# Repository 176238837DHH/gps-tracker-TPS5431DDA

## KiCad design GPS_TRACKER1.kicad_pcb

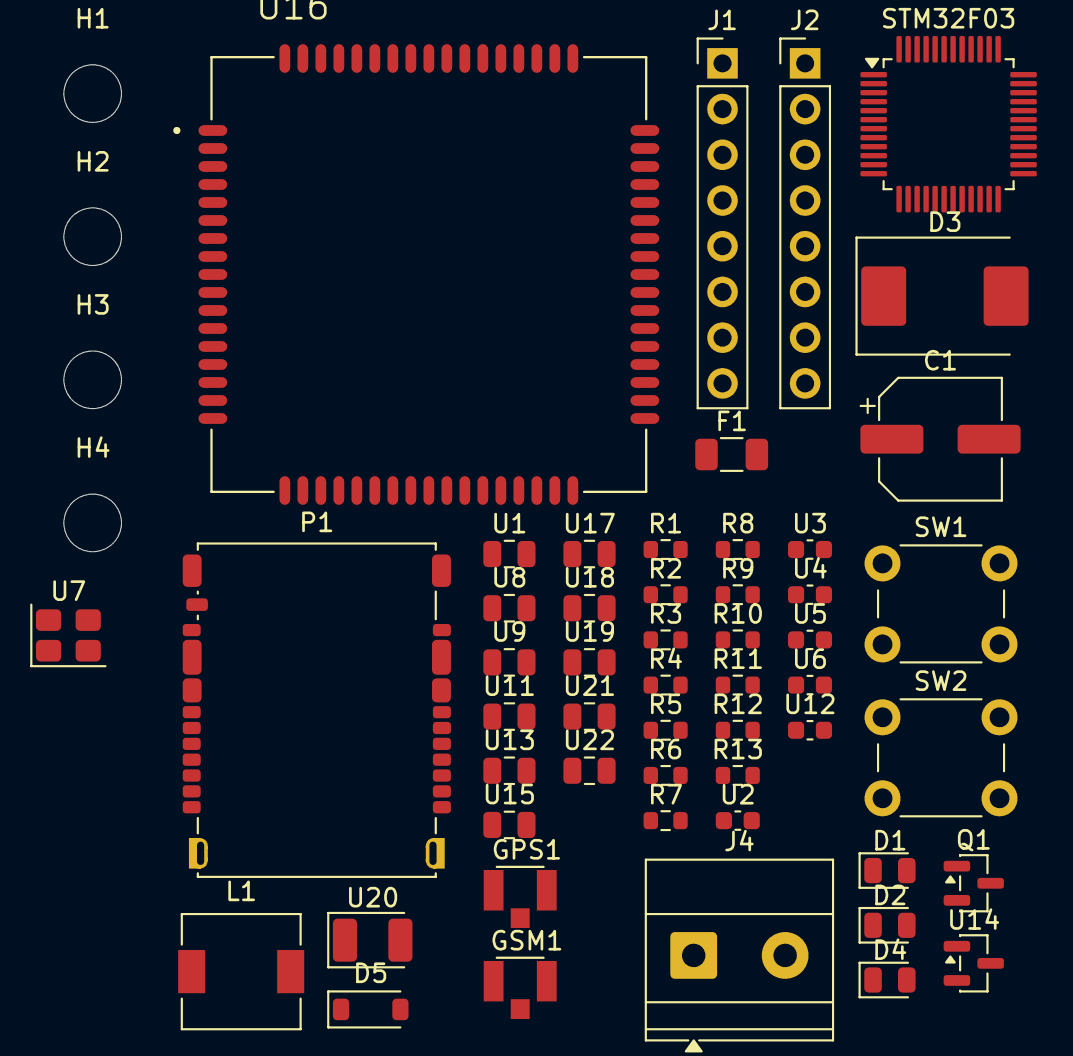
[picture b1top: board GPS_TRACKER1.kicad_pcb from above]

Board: 2 copper layers, 56 parts (0 on the bottom side), 41 nets, no tracks yet.

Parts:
C1: 220u; CP_Elec_6.3x7.7
D1, D2: LED; LED_0805_2012Metric
D3: B340A; D_SMC
D4: PWR Status; LED_0805_2012Metric
D5: D_Zener; D_SOD-123
F1: Fuse; Fuse_1206_3216Metric
GPS1: U.FL-R-SMT(10); HRS_U.FL-R-SMT_01_
GSM1: U.FL-R-SMT(10); HRS_U.FL-R-SMT_01_
H1, H2, H3, H4: MountingHole; MountingHole_3.2mm_M3
J1: Right Header Pins; PinHeader_1x08_P2.54mm_Vertical
J2: Left Header Pins; PinHeader_1x08_P2.54mm_Vertical
J4: 5V-20V; TerminalBlock_Phoenix_MKDS-1,5-2-5.08_1x02_P5.08mm_Horizont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
L1: 15 uH; L_6.3x6.3_H3
P1: SMO-1512; SD-SIM_microSD-microSIM_Molex_104168-1620
Q1: AO3407; SOT-23
R1, R2, R8, R10: 1k5; R_0603_1608Metric
R3: 10k; R_0603_1608Metric
R4, R5, R12: R; R_0603_1608Metric
R6: 1K; R_0603_1608Metric
R7: 100k; R_0603_1608Metric
R9: 8k2; R_0603_1608Metric
R11: 2k7; R_0603_1608Metric
R13: 4k7; R_0603_1608Metric
STM32F03: STM32F030C8Tx; LQFP-48_7x7mm_P0.5mm
SW1, SW2: SW_Push; SW_PUSH_6mm
U1, U17: 4u7; C_0805_2012Metric
U2, U3, U4, U5, U6, U12: 100n; C_0603_1608Metric
U7: 8MHz; Crystal_SMD_3225-4Pin_3.2x2.5mm
U8, U9: 30p; C_0805_2012Metric
U11, U22: 10p; C_0805_2012Metric
U13: 10n; C_0805_2012Metric
U14: TPS5430DDA; SOT-23
U15: 10u; C_0805_2012Metric
U16: SIM808; XCVR_SIM808
U18: 1u; C_0805_2012Metric
U19: 22p; C_0805_2012Metric
U20: 100u; CP_EIA-3528-12_Kemet-T
U21: 33p; C_0805_2012Metric

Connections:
+3.3V: C1.1, D5.1 (K), J2.8, L1.2, R8.2, R9.1, STM32F03.1 (VDD), STM32F03.9 (VDDA), STM32F03.24 (VDD), STM32F03.48 (VDD), SW2.2, U1.1, U2.1, U3.1, U4.1, U5.1, U16.4 (VBAT), U16.5 (VBAT), U16.6 (VBAT), U20.1, U21.1, U22.1
FEEDBACK: R9.2, R10.2
GND: C1.2, D1.1 (K), D2.1 (K), D3.2 (A), D4.1 (K), D5.2 (A), J1.1, J2.1, Q1.1 (G), R3.2, R7.1, R11.1, STM32F03.8 (VSSA), STM32F03.23 (VSS), STM32F03.47 (VSS), SW1.2, U1.2, U2.2, U3.2, U4.2, U5.2, U6.1, U8.2, U9.2, U11.2, U12.2, U15.2, U16.1 (GND), U16.2 (GND), U16.3 (GND), U16.18 (GND), U16.28 (GND), U16.34 (GND), U16.36 (GND), U16.40 (GND), U16.51 (GND), U16.52 (GND), U16.54 (GND), U16.64 (GND), U16.65 (GND), U16.67 (GND), U16.68 (GND), U17.1, U18.1, U19.2, U20.2, U21.2, U22.2
GPS_ANT: GPS1.3 (SIG), U16.35 (GPS_ANT)
GSM_ANT: GSM1.3 (SIG), U16.66 (GSM_ANT)
LED1: R2.1, STM32F03.25 (PB12)
LED2: R1.1, STM32F03.26 (PB13)
NRST: J1.3, STM32F03.7 (NRST), SW1.1, U6.2
unnamed: D1.2 (A), R1.2
unnamed: D2.2 (A), R2.2
unnamed: D3.1 (K), L1.1, U13.2
unnamed: D4.2 (A), R8.1
unnamed: GPS1.1 (GND), GPS1.2 (GND)
unnamed: GSM1.1 (GND), GSM1.2 (GND)
unnamed: F1.2, Q1.3 (D), U15.1
unnamed: R6.1, R7.2, SW2.1, U11.1
unnamed: R10.1, R11.2
unnamed: R3.1, STM32F03.44 (BOOT0)
unnamed: R6.2, STM32F03.22 (PB11), U12.1
unnamed: STM32F03.5 (PF0), U7.1, U8.1
unnamed: STM32F03.6 (PF1), U7.2, U9.1
unnamed: U13.1, U14.1 (BOOT)
unnamed: R13.1, U16.7 (VDD_EXT)
unnamed: U16.17 (VRTC), U17.2
PA4: J2.5, STM32F03.14 (PA4)
PA5/SPI1_CLK: J2.4, STM32F03.15 (PA5)
PA6/SPI1_MISO: J2.3, STM32F03.16 (PA6)
PA7/SPI1_MOSI: J2.2, STM32F03.17 (PA7)
SIM_CLK: R5.2, U16.31 (SIM_CLK)
SIM_DATA: R12.2, U16.30 (SIM_DATA), U19.1
SIM_DET: R13.2, U16.33 (SIM_DET)
SIM_PWRKEY: J1.8, STM32F03.46 (PB9), U16.8 (PWRKEY)
SIM_RESET: J1.5, STM32F03.36 (PF7), U16.16 (~RESET)
SIM_RST: R4.2, U16.32 (SIM_RST)
SIM_RX: J1.6, STM32F03.30 (PA9), U16.15 (RXD)
SIM_TX: J1.7, STM32F03.31 (PA10), U16.14 (TXD)
SIM_VDD: U16.29 (SIM_VDD), U18.2
STATUS: STM32F03.3 (PC14), U16.49 (STATUS)
SWDCLK: J1.4, STM32F03.37 (PA14)
USART2_RX: J2.6, STM32F03.13 (PA3)
USART2_TX: J2.7, STM32F03.12 (PA2)

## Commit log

2026-03-11 with pdf schematic
